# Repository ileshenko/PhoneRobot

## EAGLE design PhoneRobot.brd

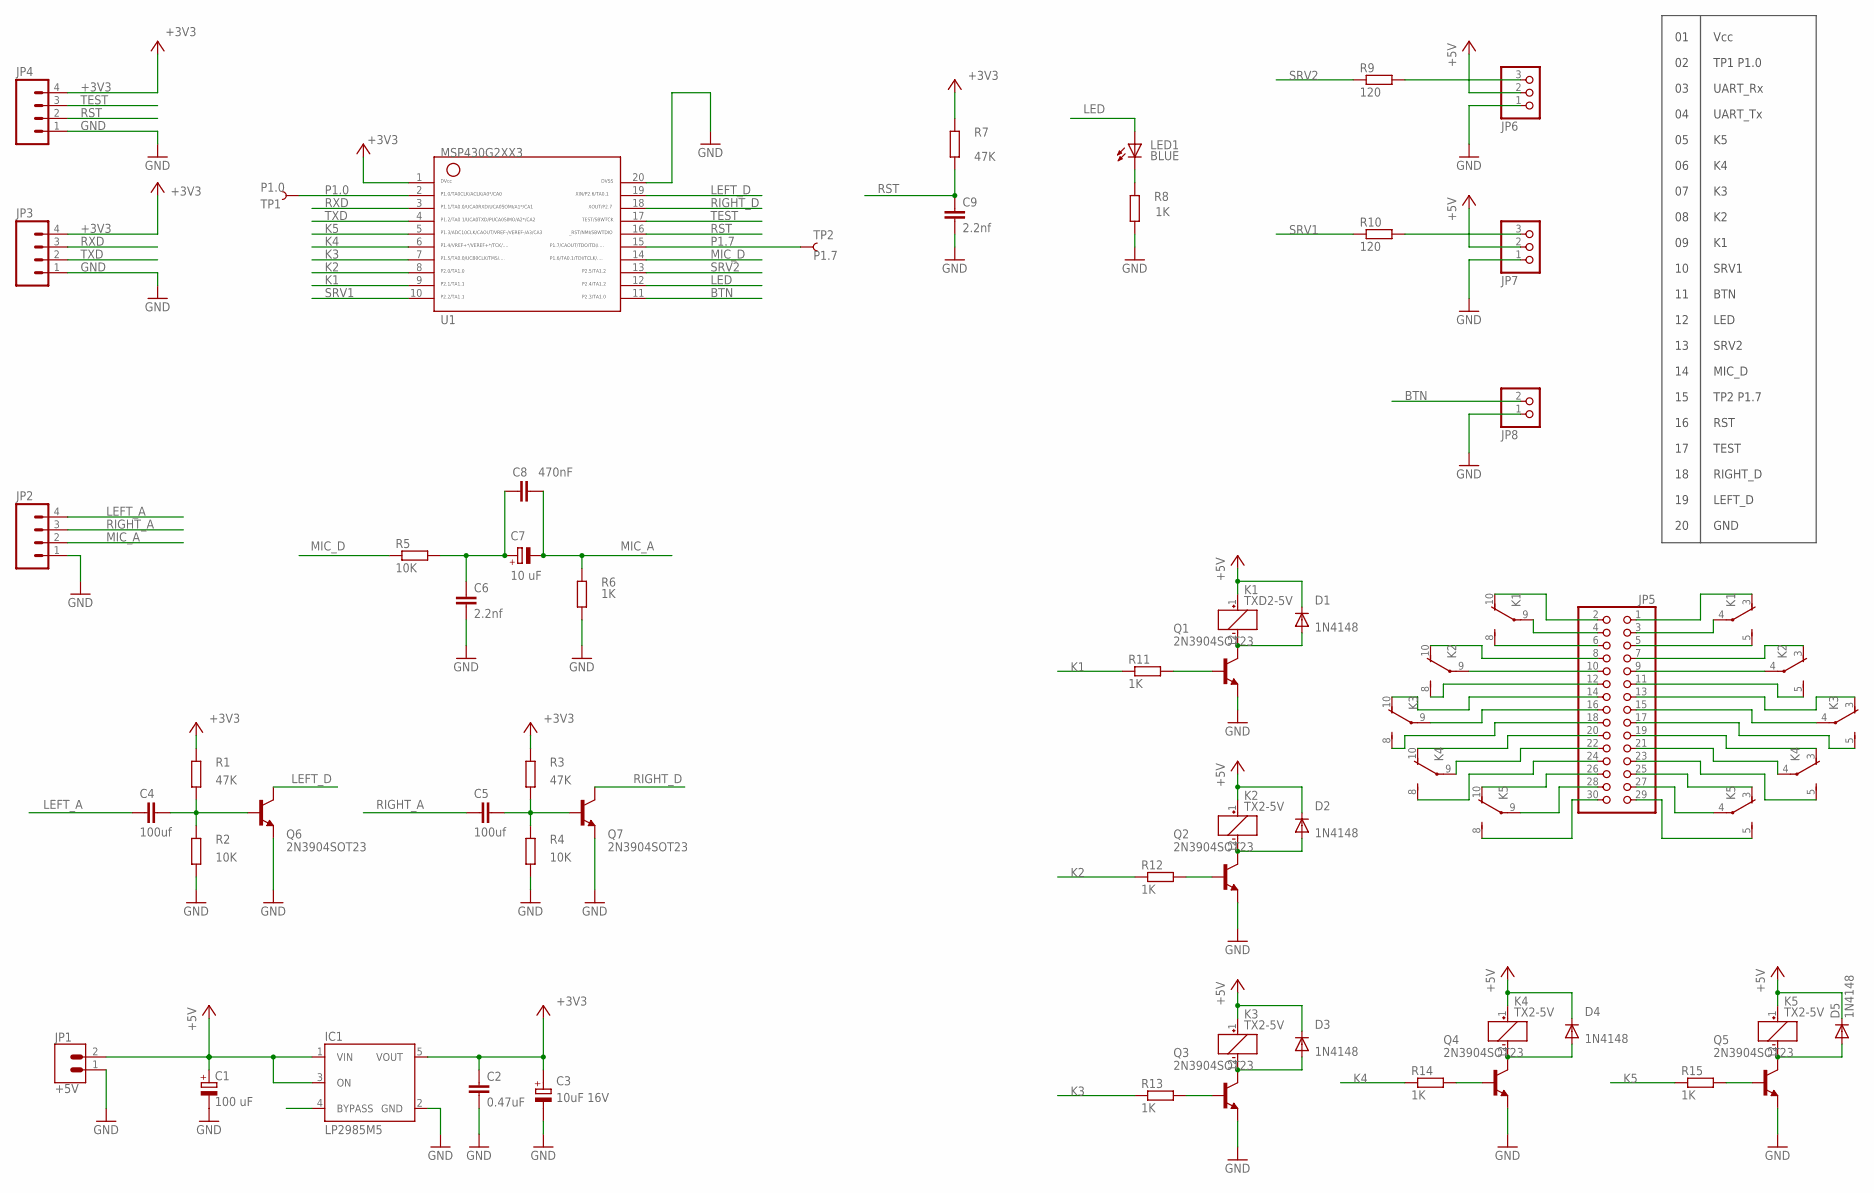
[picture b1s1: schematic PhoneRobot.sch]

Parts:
C1: 100 uF; E2,5-7
C2: 0.47uF; C0805
C3: 10uF 16V; CAPMP3216X180N
C4, C5: 100uf; C0805
C6, C9: 2.2nf; C0805
C7: 10 uF; E2,5-7
C8: 470nF; C0805
D1, D2, D3, D4, D5: 1N4148; SOD123
IC1: LP2985M5; SOT23-5
JP1: +5V; BLUE_TERM
JP2, JP3, JP4: M04PTH; 1X04
JP5: PINHD-2X15; 2X15
JP6, JP7: PINHD-1X3; 1X03
JP8: PINHD-1X2; 1X02
K1: TXD2-5V; TXD2
K2, K3, K4, K5: TX2-5V; TX2
LED1: BLUE; CHIP-LED0805
Q1, Q2, Q3, Q4, Q5, Q6, Q7: 2N3904SOT23; SOT23-BEC
R1, R3, R7: 47K; R0805
R2, R4, R5: 10K; R0805
R6, R8, R11, R12, R13, R14, R15: 1K; R0805
R9, R10: 120; R0805
TP1: P1.0; PAD.03X.03
TP2: P1.7; PAD.03X.03
U1: G2XX3---PW20; PW20

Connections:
+3V3: C2.1, C3.+, IC1.5 (VOUT), JP3.4, JP4.4, R1.2, R3.2, R7.2, U1.1
+5V: C1.+, D1.C, D2.C, D3.C, D4.C, D5.C, IC1.1 (VIN), IC1.3 (ON), JP1.2, JP6.2, JP7.2, K1.1 (+), K2.1 (+), K3.1 (+), K4.1 (+), K5.1 (+)
BTN: JP8.2, U1.11
GND: C1.-, C2.2, C3.-, C6.2, C9.2, IC1.2 (GND), JP1.1, JP2.1, JP3.1, JP4.1, JP6.1, JP7.1, JP8.1, Q1.E, Q2.E, Q3.E, Q4.E, Q5.E, Q6.E, Q7.E, R2.1, R4.1, R6.1, R8.1, U1.20
K1: R11.1, U1.9
K2: R12.1, U1.8
K3: R13.1, U1.7
K4: R14.1, U1.6
K5: R15.1, U1.5
LED: LED1.A, U1.12
LEFT_A: C4.1, JP2.4
LEFT_D: Q6.C, U1.19
MIC_A: C7.-, C8.2, JP2.2, R6.2
MIC_D: R5.1, U1.14
unnamed: C6.1, C7.+, C8.1, R5.2
unnamed: JP5.2, K1.10 (O)
unnamed: JP5.4, K1.9
unnamed: JP5.6, K1.8 (S)
unnamed: JP5.3, K1.4
unnamed: JP6.3, R9.2
unnamed: JP5.1, K1.3 (O)
unnamed: JP5.5, K1.5 (S)
unnamed: D1.A, K1.12 (-), Q1.C
unnamed: Q1.B, R11.2
unnamed: C4.2, Q6.B, R1.1, R2.2
unnamed: JP5.9, K2.4
unnamed: JP5.7, K2.3 (O)
unnamed: JP5.11, K2.5 (S)
unnamed: JP5.13, K3.3 (O)
unnamed: JP5.15, K3.4
unnamed: JP5.17, K3.5 (S)
unnamed: JP5.19, K4.3 (O)
unnamed: JP5.21, K4.4
unnamed: JP5.23, K4.5 (S)
unnamed: JP5.25, K5.3 (O)
unnamed: LED1.C, R8.2
unnamed: JP5.27, K5.4
unnamed: JP5.29, K5.5 (S)
unnamed: JP5.10, K2.9
unnamed: JP5.8, K2.10 (O)
unnamed: JP5.12, K2.8 (S)
unnamed: JP5.30, K5.8 (S)
unnamed: JP5.28, K5.9
unnamed: JP5.26, K5.10 (O)
unnamed: JP5.24, K4.8 (S)
unnamed: JP5.22, K4.9
unnamed: JP5.20, K4.10 (O)
unnamed: JP5.18, K3.8 (S)
unnamed: JP5.16, K3.9
unnamed: JP5.14, K3.10 (O)
unnamed: D2.A, K2.12 (-), Q2.C
unnamed: D3.A, K3.12 (-), Q3.C
unnamed: D5.A, K5.12 (-), Q5.C
unnamed: D4.A, K4.12 (-), Q4.C
unnamed: Q5.B, R15.2
unnamed: Q4.B, R14.2
unnamed: Q3.B, R13.2
unnamed: Q2.B, R12.2
unnamed: C5.2, Q7.B, R3.1, R4.2
unnamed: JP7.3, R10.2
P1.0: TP1.P$1, U1.2
P1.7: TP2.P$1, U1.15
RIGHT_A: C5.1, JP2.3
RIGHT_D: Q7.C, U1.18
RST: C9.1, JP4.2, R7.1, U1.16
RXD: JP3.3, U1.3
SRV1: R10.1, U1.10
SRV2: R9.1, U1.13
TEST: JP4.3, U1.17
TXD: JP3.2, U1.4

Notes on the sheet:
Vcc
GND
UART_Rx
SRV2
RIGHT_D
MIC_D
TP2 P1.7
LEFT_D
UART_Tx
RST
TEST
TP1 P1.0
SRV1
LED
BTN

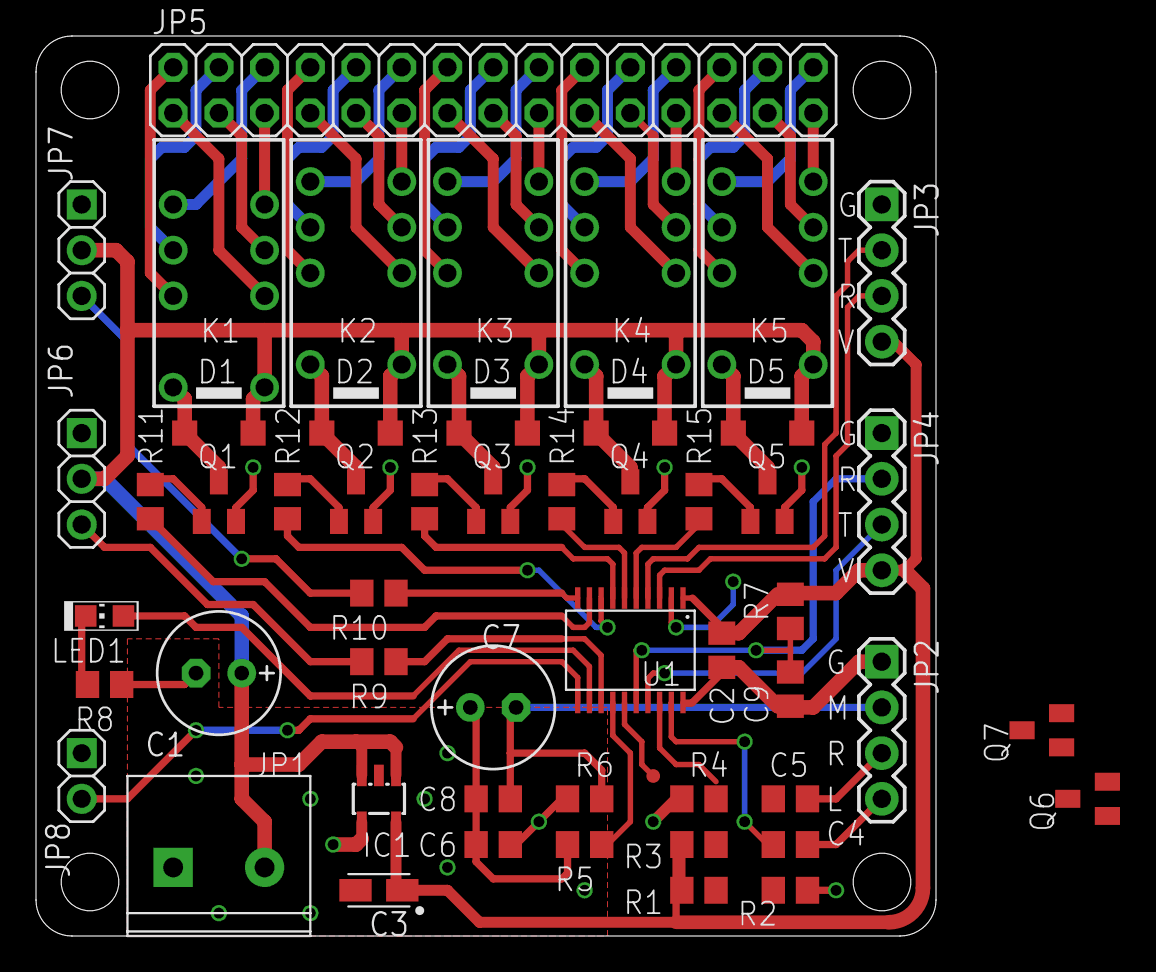
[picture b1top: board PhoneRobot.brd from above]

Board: 2 copper layers, 50.0 x 50.0 mm, 54 parts (0 on the bottom side), 70 nets.

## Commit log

2014-03-08 first version for POC
2014-04-04 write description on the bottom of the PCB
2014-04-06 Nominals changed after soldering first version
2014-04-15 Initial version
    Demomode works with analog coding - different frequences for each
    direction and speed
2014-04-15 Fix Audio Input schematics
    Schematics only, needs to fix layout
2014-04-19 Add PWM support

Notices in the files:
parts and their libraries:
SparkFun: Licensing: CC v3.0 Share-Alike You are welcome to use this library for commercial purposes.
